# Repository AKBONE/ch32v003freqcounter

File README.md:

# ch32v003freqcounter

This is an electronic construction kit teaching material for kids' science experiment classes.
## Sound learning

It takes in sound, counts the frequencies, and displays them.

Learn what frequency various sounds are,
You can learn how the Doppler effect is generated by motion to a sound source.

In the future, the system will be able to display waveforms, measure ultrasonic frequencies, and output sounds of arbitrary frequencies.
This will allow students to learn that sound is a wave, that sounds are not audible to humans, and that different sounds can be heard at different ages.

## Concept
We try to make the kit as inexpensive as possible. We try to make the kit as inexpensive as possible and use inexpensive microcontrollers for this purpose.

## Soldering Training
The main components are soldered at the factory during manufacturing. The remaining few through-hole parts are made to be completed by soldering.

## Applications

With its small footprint and fast screen display, it can be used as a small signage.

# Circuit

## Schematic

## artdesign

# pin assign

| CH32V003F4P6 PIN |           | OLED PIN | OLED |
|------------------|-----------|----------|------|
|                  |           | 1        | GND  |
|                  |           | 2        | 3.3V |
| 15               |           | 3        | D0   |
| 16               | MOSI       | 4        | D1   |
| 17               | PC7(MISO) | 5        | RST  |
| 14               | PC4      | 6        | DC   |
| 13               | PC3       | 7        | CS   |

| CH32V003F4P6 PIN |       | PROGRAM PIN |   | LED(D1) |         |
|------------------|-------|-------------|-------|---------|---------|
|                  |       | 1           | 3.3V  |         |         |
| 18               | SWDIO | 2           | SWDIO |         |         |
|                  |       | 3           | GND   |         | CATHODE |
| 4                | NRST  | 4           | RST   |         |         |
| 2                | UTX   | 5           | TX    |         | ANODE   |
| 3                | URX   | 6           | RX    |         |         |

| CH32V003F4P6 PIN |           | SW  |  |
|------------------|-----------|-----|------|
| 8                | PD0       | SW1 | OK   |
| 10               | PC0       | SW2 | ↓    |
| 1                | PD4       | SW3 | ↑    |

| CH32V003F4P6 PIN |         | SEEED_GROVE |    |
|------------------|---------|-------------|--------|
| 12               | PC2/SCL | 1           | YELLOW |
| 11               | PC1/SDA | 2           | WHITE  |
|                  |         | 3           | 3.3V   |
|                  |         | 4           | GND    |

| CH32V003F4P6 PIN |        | NAX4466_MIC_MODULE |  |
|------------------|--------|--------------------|------|
| 20               | PD3/A4 | 1                  | OUT  |
|                  |        | 2                  | GND  |
|                  |        | 3                  | 3.3V |

| CH32V003F4P6 PIN |      | SPEAKER |  |
|------------------|------|---------|------|
|                  |      | 1       | GND  |
| 19               | PD2  | 2       | IN   |

## Links
- [ユーザ向けポータルサイト](https://akbone.github.io/ch32v003freqcounter/)
- [50円マイコン ch32v003 を使った簡単キット(AKBONE2024)を組み立てる #RISC-V - Qiita](https://qiita.com/nanbuwks/items/22680849ee7674d66a89)

### For Engineer
- [AKBONE/ch32v003freqcounter](https://github.com/AKBONE/ch32v003freqcounter)
- [cnlohr/ch32v003fun: Open source minimal stack for the ch32 line of WCH processors, including the ch32v003, a 10¢ 48 MHz RISC-V Microcontroller - as well as many other chips within the ch32v/x line.](https://github.com/cnlohr/ch32v003fun)

#### Parts
- [32ビットRISC-Vマイコン CH32V003F4P6: 半導体 秋月電子通商-電子部品・ネット通販](https://akizukidenshi.com/catalog/g/g118061/)
  - [データシート](https://akizukidenshi.com/goodsaffix/CH32V003.pdf)

# License

Public Domain ((cc0)
However, libraries used are subject to individual licenses.

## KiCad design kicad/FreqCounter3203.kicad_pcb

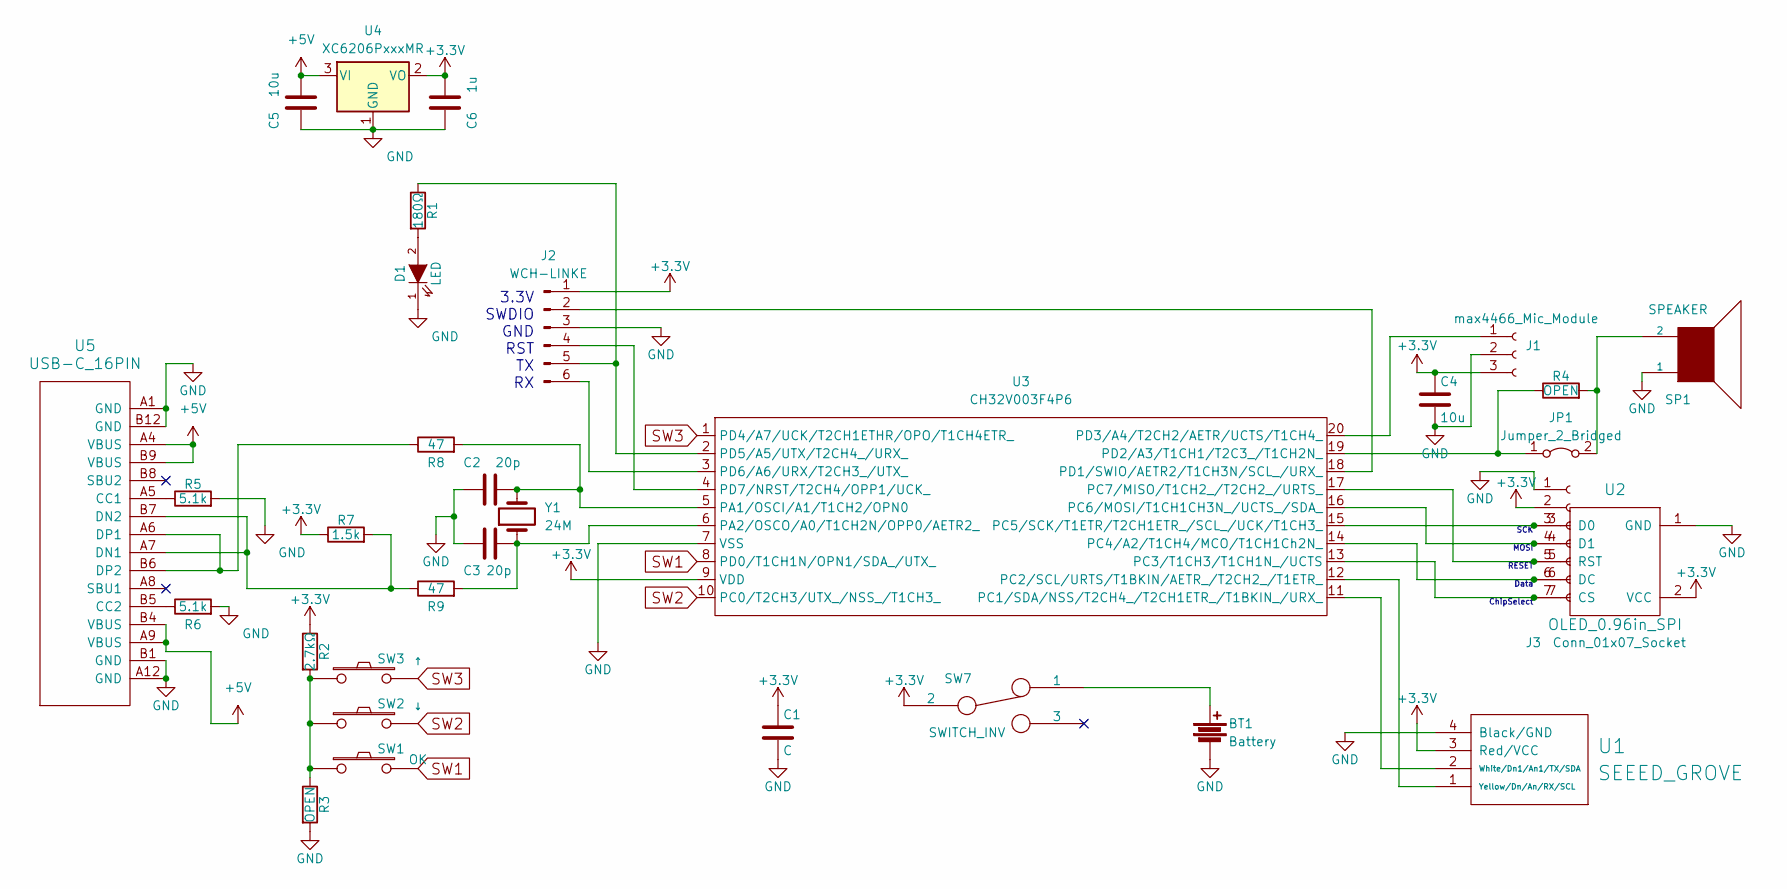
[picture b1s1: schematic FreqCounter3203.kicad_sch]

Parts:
BT1: Battery; BatteryHolder_Keystone_3002_1x2032
C1: C; C_0603_1608Metric
C2, C3: 20p; C_0603_1608Metric
C4, C5: 10u; C_0603_1608Metric
C6: 1u; C_0603_1608Metric
D1: LED; LED_D3.0mm
J1: max4466_Mic_Module; PinHeader_1x03_P2.54mm_Vertical
J2: WCH-LINKE; PinHeader_1x06_P2.54mm_Vertical
J3: Conn_01x07_Socket; PinSocket_1x07_P2.54mm_Vertical
JP1: Jumper_2_Bridged; SolderJumper-2_P1.3mm_Bridged_Pad1.0x1.5mm
R1: 180Ω; R_0603_1608Metric
R2: 2.7kΩ; R_0603_1608Metric
R3, R4: OPEN; R_0603_1608Metric
R5, R6: 5.1k; R_0603_1608Metric
R7: 1.5k; R_0603_1608Metric
R8, R9: 47; R_0603_1608Metric
SP1: SPEAKER; Buzzer_TDK_PS1240P02BT_D12.2mm_H6.5mm
SW1: OK; SW_Push_1P1T_NO_6x6mm_H9.5mm
SW2: ↓; SW_Push_1P1T_NO_6x6mm_H9.5mm
SW3: ↑; SW_Push_1P1T_NO_6x6mm_H9.5mm
SW7: SWITCH_INV; PinHeader_1x03_P2.54mm_Vertical
U1: SEEED_GROVE; JST_PH_B4B-PH-K_1x04_P2.00mm_Vertical
U2: OLED_0.96in_SPI
U3: CH32V003F4P6; TSSOP-20_4.4x6.5mm_P0.65mm
U4: XC6206PxxxMR; SOT-23-3
U5: USB-C_16PIN; USB_Type_C_16Pin_Female
Y1: 24M; Crystal_SMD_HC49-SD

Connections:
+3V3: C1.1, C4.1, C6.2, J1.3, J2.1, J3.2, R2.1, R7.1, SW7.2, U1.3 (Red/VCC), U2.2 (VCC), U3.9 (VDD), U4.2 (VO)
+5V: C5.2, U4.3 (VI), U5.A4 (VBUS), U5.A9 (VBUS), U5.B4 (VBUS), U5.B9 (VBUS)
GND: BT1.2, C1.2, C2.1, C3.1, C4.2, C5.1, C6.1, D1.1 (K), J1.2, J2.3, J3.1, R3.2, R5.2, R6.2, SP1.1, U1.4 (Black/GND), U2.1 (GND), U3.7 (VSS), U4.1 (GND), U5.A1 (GND), U5.A12 (GND), U5.B1 (GND), U5.B12 (GND)
unnamed: BT1.1, SW7.1
unnamed: D1.2 (A), R1.2
unnamed: J1.1, U3.20 (PD3/A4/T2CH2/AETR/UCTS/T1CH4_)
unnamed: J2.2, U3.18 (PD1/SWIO/AETR2/T1CH3N/SCL_/URX_)
unnamed: J2.4, U3.4 (PD7/NRST/T2CH4/OPP1/UCK_)
unnamed: J2.5, R1.1, U3.2 (PD5/A5/UTX/T2CH4_/URX_)
unnamed: J2.6, U3.3 (PD6/A6/URX/T2CH3_/UTX_)
unnamed: J3.3, U2.3 (D0), U3.15 (PC5/SCK/T1ETR/T2CH1ETR_/SCL_/UCK/T1CH3_)
unnamed: J3.4, U2.4 (D1), U3.16 (PC6/MOSI/T1CH1CH3N_/UCTS_/SDA_)
unnamed: J3.5, U2.5 (RST), U3.17 (PC7/MISO/T1CH2_/T2CH2_/URTS_)
unnamed: J3.6, U2.6 (DC), U3.14 (PC4/A2/T1CH4/MCO/T1CH1Ch2N_)
unnamed: J3.7, U2.7 (CS), U3.13 (PC3/T1CH3/T1CH1N_/UCTS)
unnamed: JP1.1 (A), R4.1, U3.19 (PD2/A3/T1CH1/T2C3_/T1CH2N_)
unnamed: JP1.2 (B), R4.2, SP1.2
unnamed: R2.2, R3.1, SW1.1, SW2.1, SW3.1
unnamed: U1.2 (White/Dn1/An1/TX/SDA), U3.11 (PC1/SDA/NSS/T2CH4_/T2CH1ETR_/T1BKIN_/UR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)
unnamed: U1.1 (Yellow/Dn/An/RX/SCL), U3.12 (PC2/SCL/URTS/T1BKIN/AETR_/T2CH2_/T1ETR_)
unnamed: C2.2, R8.2, U3.5 (PA1/OSCI/A1/T1CH2/OPN0), Y1.2
unnamed: C3.2, R9.2, U3.6 (PA2/OSCO/A0/T1CH2N/OPP0/AETR2_), Y1.1
unnamed: R5.1, U5.A5 (CC1)
unnamed: R6.1, U5.B5 (CC2)
unnamed: R7.2, R9.1, U5.A7 (DN1), U5.B7 (DN2)
unnamed: R8.1, U5.A6 (DP1), U5.B6 (DP2)
SW1: SW1.2, U3.8 (PD0/T1CH1N/OPN1/SDA_/UTX_)
SW2: SW2.2, U3.10 (PC0/T2CH3/UTX_/NSS_/T1CH3_)
SW3: SW3.2, U3.1 (PD4/A7/UCK/T2CH1ETHR/OPO/T1CH4ETR_)

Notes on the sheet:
3.3V SWDIO GND RST TX RX
SCK MOSI RESET Data ChipSelect

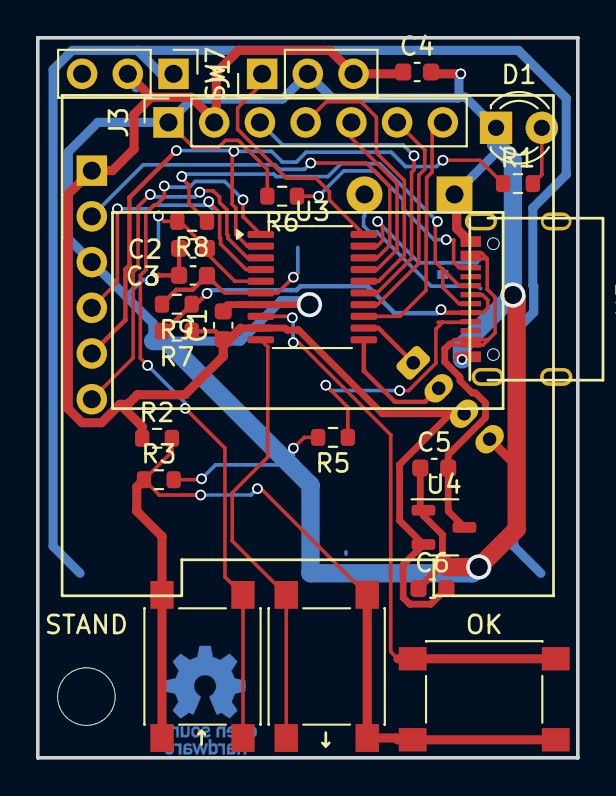
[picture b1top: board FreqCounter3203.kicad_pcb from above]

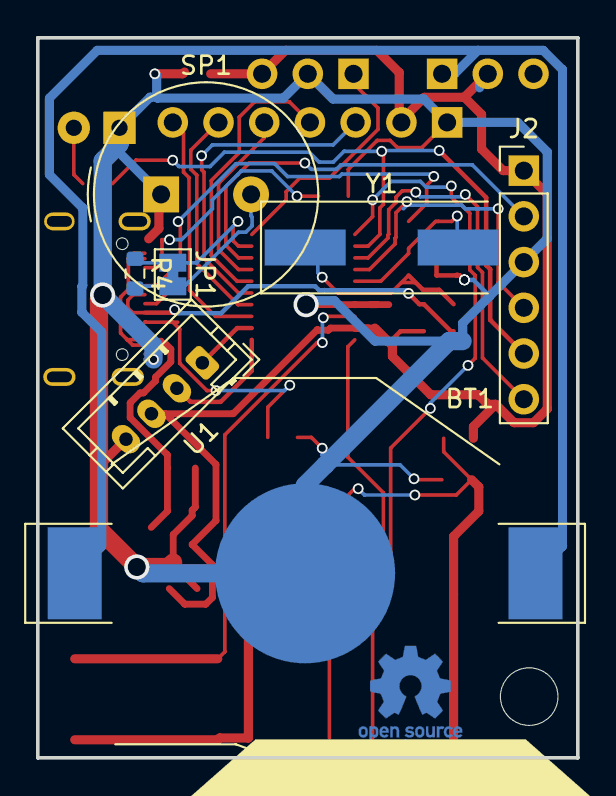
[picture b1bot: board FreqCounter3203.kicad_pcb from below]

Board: 2 copper layers, 30.0 x 40.0 mm, 32 parts (7 on the bottom side), 29 nets.

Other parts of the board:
STAND: MountingHole_3mm

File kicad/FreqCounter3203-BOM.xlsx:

Comment | Designator | Footprint
2.7kΩ | R2 | R_0603_1608Metric | C13167
47 | R9,R8 | R_0603_1608Metric | C23179
1u | C6 | C_0603_1608Metric | C59302
20p | C2,C3 | C_0603_1608Metric | C165732
10u | C4,C5 | C_0603_1608Metric | C38898
0.1u | C1 | C_0603_1608Metric | C14663
XC6206PxxxMR | U4 | SOT-23-3 | C5446
5.1k | R5,R6 | R_0603_1608Metric | c23186
TACTSWWITCH | SW1,SW2,SW3 | SW_Push_1P1T_NO_6x6mm_H9.5mm | c2837533
180Ω | R1 | R_0603_1608Metric | c22828
CH32V003F4P6 | U3 | TSSOP-20_4.4x6.5mm_P0.65mm | c5187096
1.5k | R7 | R_0603_1608Metric | c22843
USB-C_16PIN | U5 | USB_Type_C_16Pin_Female | c393939
Battery | BT1 | BatteryHolder_Keystone_3002_1x2032 | c964834
LED | D1 | LED_D3.0mm | C2895470
SEEED_GROVE | U1 | JST_PH_B4B-PH-K_1x04_P2.00mm_Vertical | C722737

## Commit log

2024-07-28 add KiCad files
2024-07-30 add sample source
2024-07-30 change kicad files
2024-07-30 update README and workshop verious lealfets.
2024-07-30 typo fix
2024-07-31 firmware first commit
2024-07-31 add ssd1306_spi.h to src folder
2024-08-01 change MIC module OUT pin assign
2024-08-01 add initial menu
2024-08-01 extract freqcounter setup and loop as functions
2024-08-01 rename file
2024-08-02 [WIP] add tone mode
2024-08-02 add realtime mode
2024-08-03 add qr tools
2024-08-03 [WIP] add index.md for GitHub Pages
2024-08-03 [WIP] add 2024-08-04/index.md for GitHub Pages
2024-08-03 change routing for GitHub Pages
2024-08-03 add event link to home page
2024-08-03 shrink memory usage footprint
2024-08-03 [WIP] add QR code mode (QR code data is dummy)
2024-08-03 change QR code data
2024-08-03 fix initial menu
2024-08-03 fix switch bug
2024-08-03 toggle up/down switch direction
2024-08-03 change sprintf to mini_snprintf for shrinking memory usage footprint
2024-08-03 change initial menu order and labels. remove menu item not implemented
2024-08-03 improve accuracy for tone mode
2024-08-03 fix realtime mode bug
2024-08-03 improve realtime mode UI
2024-08-04 development branch by ooe
2024-08-04 change version number
2024-08-05 support micros() and millis() by SysTick
2024-08-05 remove local variables
2024-08-06 Update README.md
    SW assign explain bug
2024-08-06 fix frequency calculation in tone mode
2024-08-06 change variable type in tone mode
2024-08-10 improve initial menu
2024-08-10 imprement LED flash feature in tone mode
2024-08-15 change doc, pictures
2024-08-15 change github pages
2024-08-15 change docs
2024-08-15 chanage README
2024-08-15 modify docs
2024-08-15 docs bug fix
2024-08-16 fix FFT bug
2024-08-16 fix version number
2024-11-09 micros() bug fix
